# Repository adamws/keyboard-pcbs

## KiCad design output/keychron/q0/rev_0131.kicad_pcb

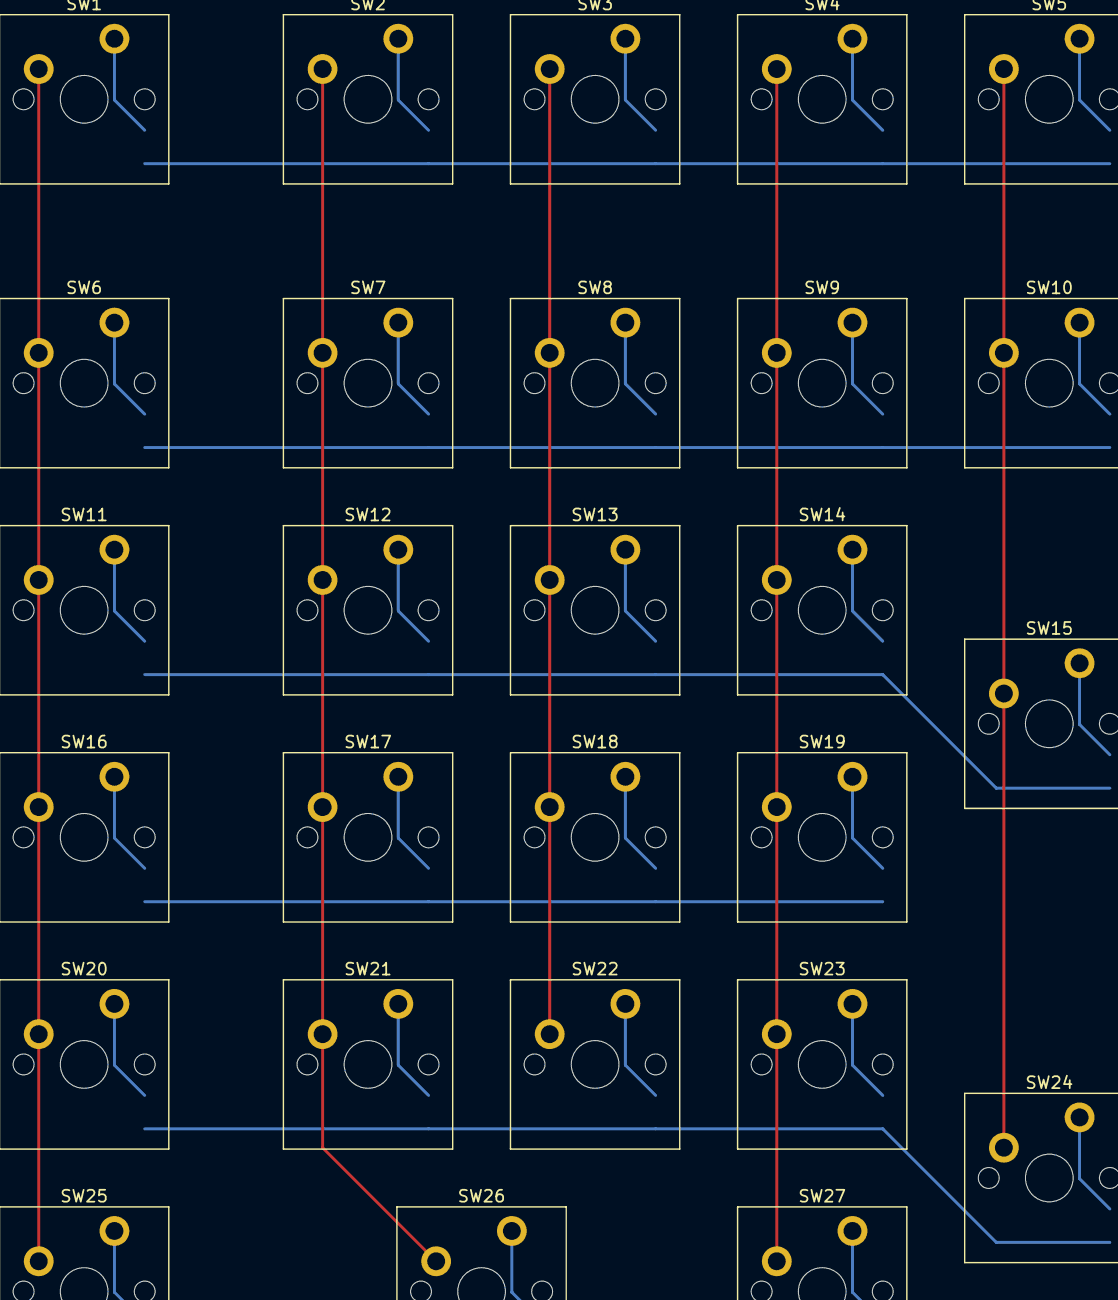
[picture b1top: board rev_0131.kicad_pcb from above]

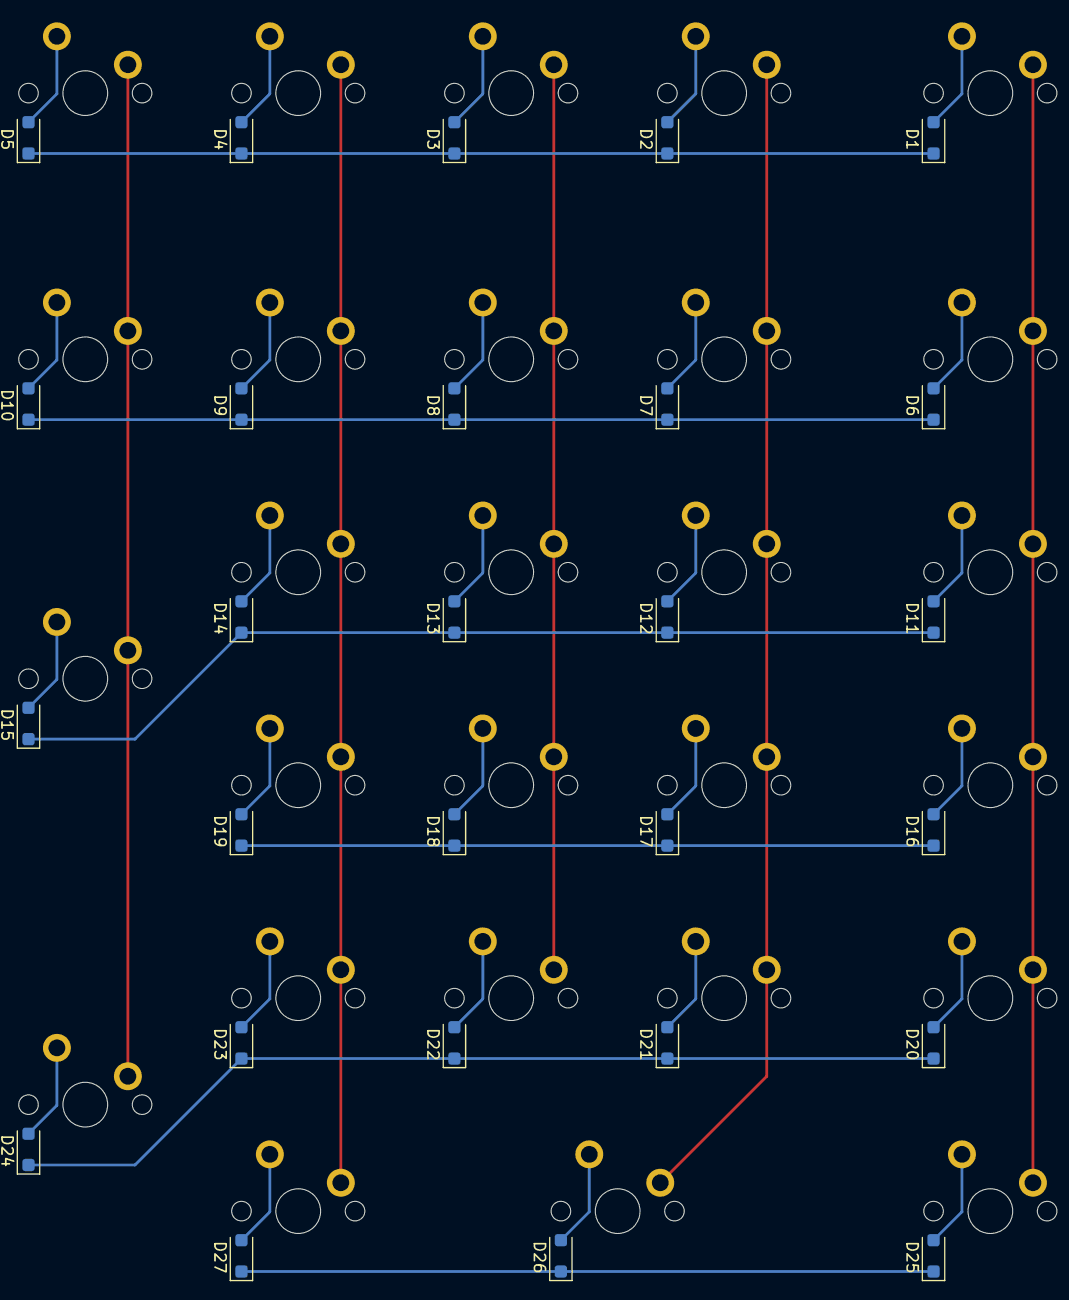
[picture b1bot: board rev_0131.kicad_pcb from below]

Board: 2 copper layers, 54 parts (27 on the bottom side), 38 nets.

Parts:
D1, D2, D3, D4, D5, D6, D7, D8, D9, D10, D11, D12, D13, D14, D15, D16, D17, D18, D19, D20, D21, D22, D23, D24, D25, D26, D27: D_SOD-123F
SW1, SW2, SW3, SW4, SW5, SW6, SW7, SW8, SW9, SW10, SW11, SW12, SW13, SW14, SW15, SW16, SW17, SW18, SW19, SW20, SW21, SW22, SW23, SW24, SW25, SW26, SW27: SW_Cherry_MX_PCB_1.00u

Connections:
COL0: SW1.1, SW6.1, SW11.1, SW16.1, SW20.1, SW25.1
COL1: SW2.1, SW7.1, SW12.1, SW17.1, SW21.1, SW26.1
COL2: SW3.1, SW8.1, SW13.1, SW18.1, SW22.1
COL3: SW4.1, SW9.1, SW14.1, SW19.1, SW23.1, SW27.1
COL4: SW5.1, SW10.1, SW15.1, SW24.1
unnamed: D1.2, SW1.2
unnamed: D2.2, SW2.2
unnamed: D3.2, SW3.2
unnamed: D4.2, SW4.2
unnamed: D5.2, SW5.2
unnamed: D6.2, SW6.2
unnamed: D7.2, SW7.2
unnamed: D8.2, SW8.2
unnamed: D9.2, SW9.2
unnamed: D10.2, SW10.2
unnamed: D11.2, SW11.2
unnamed: D12.2, SW12.2
unnamed: D13.2, SW13.2
unnamed: D14.2, SW14.2
unnamed: D15.2, SW15.2
unnamed: D16.2, SW16.2
unnamed: D17.2, SW17.2
unnamed: D18.2, SW18.2
unnamed: D19.2, SW19.2
unnamed: D20.2, SW20.2
unnamed: D21.2, SW21.2
unnamed: D22.2, SW22.2
unnamed: D23.2, SW23.2
unnamed: D24.2, SW24.2
unnamed: D25.2, SW25.2
unnamed: D26.2, SW26.2
unnamed: D27.2, SW27.2
ROW0: D1.1, D2.1, D3.1, D4.1, D5.1
ROW1: D6.1, D7.1, D8.1, D9.1, D10.1
ROW2: D11.1, D12.1, D13.1, D14.1, D15.1
ROW3: D16.1, D17.1, D18.1, D19.1
ROW4: D20.1, D21.1, D22.1, D23.1, D24.1
ROW5: D25.1, D26.1, D27.1

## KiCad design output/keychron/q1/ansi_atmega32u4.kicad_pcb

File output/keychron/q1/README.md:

## keychron/q1/ansi_atmega32u4

[layout](ansi_atmega32u4-kle.json) - [PCB](ansi_atmega32u4.kicad_pcb)

{:loading="lazy"}

[Open in keyboard-layout-editor](http://www.keyboard-layout-editor.com/##@@_c=#777777;&=0,0%0AESC&_x:0.25&c=#cccccc;&=0,2&=0,3&=0,4&=0,5&_x:0.25&c=#aaaaaa;&=0,6&=0,7&=0,8&=0,9&_x:0.25&c=#cccccc;&=0,10&=0,11&=0,12&=0,13&_x:0.25&c=#aaaaaa;&=4,14&_x:0.25;&=0,14;&@_y:0.25&c=#cccccc;&=1,0&=1,1&=1,2&=1,3&=1,4&=1,5&=1,6&=1,7&=1,8&=1,9&=1,10&=1,11&=1,12&_c=#aaaaaa&w:2;&=1,13&_x:0.25;&=1,14;&@_w:1.5;&=2,0&_c=#cccccc;&=2,1&=2,2&=2,3&=2,4&=2,5&=2,6&=2,7&=2,8&=2,9&=2,10&=2,11&=2,12&_w:1.5;&=2,13&_x:0.25&c=#aaaaaa;&=2,14;&@_w:1.75;&=3,0&_c=#cccccc;&=3,1&=3,2&=3,3&=3,4&=3,5&=3,6&=3,7&=3,8&=3,9&=3,10&=3,11&_c=#777777&w:2.25;&=3,13&_x:0.25&c=#aaaaaa;&=3,14;&@_w:2.25;&=4,0&_c=#cccccc;&=4,2&=4,3&=4,4&=4,5&=4,6&=4,7&=4,8&=4,9&=4,10&=4,11&_c=#aaaaaa&w:1.75;&=4,13;&@_x:14.25&y:-0.75;&=3,12;&@_y:-0.25&w:1.25;&=5,0&_w:1.25;&=5,1&_w:1.25;&=5,2&_c=#cccccc&w:6.25;&=5,6&_c=#aaaaaa;&=5,10&=5,11&=5,12;&@_x:13.25&y:-0.75;&=5,13&=4,12&=5,14)

{:loading="lazy"}

## keychron/q1/ansi_atmega32u4_encoder

[layout](ansi_atmega32u4_encoder-kle.json) - [PCB](ansi_atmega32u4_encoder.kicad_pcb)

{:loading="lazy"}

[Open in keyboard-layout-editor](http://www.keyboard-layout-editor.com/##@@_c=#777777;&=0,0%0AESC&_x:0.25&c=#cccccc;&=0,2&=0,3&=0,4&=0,5&_x:0.25&c=#aaaaaa;&=0,6&=0,7&=0,8&=0,9&_x:0.25&c=#cccccc;&=0,10&=0,11&=0,12&=0,13&_x:0.25&c=#aaaaaa;&=4,14&_x:0.25;&=0,14%0A%0A%0A%0A%0A%0A%0A%0A%0Ae0;&@_y:0.25&c=#cccccc;&=1,0&=1,1&=1,2&=1,3&=1,4&=1,5&=1,6&=1,7&=1,8&=1,9&=1,10&=1,11&=1,12&_c=#aaaaaa&w:2;&=1,13&_x:0.25;&=1,14;&@_w:1.5;&=2,0&_c=#cccccc;&=2,1&=2,2&=2,3&=2,4&=2,5&=2,6&=2,7&=2,8&=2,9&=2,10&=2,11&=2,12&_w:1.5;&=2,13&_x:0.25&c=#aaaaaa;&=2,14;&@_w:1.75;&=3,0&_c=#cccccc;&=3,1&=3,2&=3,3&=3,4&=3,5&=3,6&=3,7&=3,8&=3,9&=3,10&=3,11&_c=#777777&w:2.25;&=3,13&_x:0.25&c=#aaaaaa;&=3,14;&@_w:2.25;&=4,0&_c=#cccccc;&=4,2&=4,3&=4,4&=4,5&=4,6&=4,7&=4,8&=4,9&=4,10&=4,11&_c=#aaaaaa&w:1.75;&=4,13;&@_x:14.25&y:-0.75;&=3,12;&@_y:-0.25&w:1.25;&=5,0&_w:1.25;&=5,1&_w:1.25;&=5,2&_c=#cccccc&w:6.25;&=5,6&_c=#aaaaaa;&=5,10&=5,11&=5,12;&@_x:13.25&y:-0.75;&=5,13&=4,12&=5,14)

{:loading="lazy"}

## keychron/q1/ansi_stm32l432

[layout](ansi_stm32l432-kle.json) - [PCB](ansi_stm32l432.kicad_pcb)

{:loading="lazy"}

[Open in keyboard-layout-editor](http://www.keyboard-layout-editor.com/##@@_c=#777777;&=0,0%0AESC&_x:0.25&c=#cccccc;&=0,1&=0,2&=0,3&=0,4&_x:0.25&c=#aaaaaa;&=0,5&=0,6&=0,7&=0,8&_x:0.25&c=#cccccc;&=0,9&=0,10&=0,11&=0,12&_x:0.25&c=#aaaaaa;&=0,13&_x:0.25;&=0,15;&@_y:0.25&c=#cccccc;&=1,0&=1,1&=1,2&=1,3&=1,4&=1,5&=1,6&=1,7&=1,8&=1,9&=1,10&=1,11&=1,12&_c=#aaaaaa&w:2;&=1,13&_x:0.25;&=1,15;&@_w:1.5;&=2,0&_c=#cccccc;&=2,1&=2,2&=2,3&=2,4&=2,5&=2,6&=2,7&=2,8&=2,9&=2,10&=2,11&=2,12&_w:1.5;&=2,13&_x:0.25&c=#aaaaaa;&=2,15;&@_w:1.75;&=3,0&_c=#cccccc;&=3,1&=3,2&=3,3&=3,4&=3,5&=3,6&=3,7&=3,8&=3,9&=3,10&=3,11&_c=#777777&w:2.25;&=3,13&_x:0.25&c=#aaaaaa;&=3,15;&@_w:2.25;&=4,0&_c=#cccccc;&=4,2&=4,3&=4,4&=4,5&=4,6&=4,7&=4,8&=4,9&=4,10&=4,11&_c=#aaaaaa&w:1.75;&=4,13;&@_x:14.25&y:-0.75&c=#777777;&=4,14;&@_y:-0.25&c=#aaaaaa&w:1.25;&=5,0&_w:1.25;&=5,1&_w:1.25;&=5,2&_c=#cccccc&w:6.25;&=5,6&_c=#aaaaaa;&=5,10&=5,11&=5,12;&@_x:13.25&y:-0.75&c=#777777;&=5,13&=5,14&=5,15)

{:loading="lazy"}

## keychron/q1/ansi_stm32l432_encoder

[layout](ansi_stm32l432_encoder-kle.json) - [PCB](ansi_stm32l432_encoder.kicad_pcb)

{:loading="lazy"}

[Open in keyboard-layout-editor](http://www.keyboard-layout-editor.com/##@@_c=#777777;&=0,0%0AESC&_x:0.25&c=#cccccc;&=0,1&=0,2&=0,3&=0,4&_x:0.25&c=#aaaaaa;&=0,5&=0,6&=0,7&=0,8&_x:0.25&c=#cccccc;&=0,9&=0,10&=0,11&=0,12&_x:0.25&c=#aaaaaa;&=0,13&_x:0.25;&=0,15%0A%0A%0A%0A%0A%0A%0A%0A%0Ae0;&@_y:0.25&c=#cccccc;&=1,0&=1,1&=1,2&=1,3&=1,4&=1,5&=1,6&=1,7&=1,8&=1,9&=1,10&=1,11&=1,12&_c=#aaaaaa&w:2;&=1,13&_x:0.25;&=1,15;&@_w:1.5;&=2,0&_c=#cccccc;&=2,1&=2,2&=2,3&=2,4&=2,5&=2,6&=2,7&=2,8&=2,9&=2,10&=2,11&=2,12&_w:1.5;&=2,13&_x:0.25&c=#aaaaaa;&=2,15;&@_w:1.75;&=3,0&_c=#cccccc;&=3,1&=3,2&=3,3&=3,4&=3,5&=3,6&=3,7&=3,8&=3,9&=3,10&=3,11&_c=#777777&w:2.25;&=3,13&_x:0.25&c=#aaaaaa;&=3,15;&@_w:2.25;&=4,0&_c=#cccccc;&=4,2&=4,3&=4,4&=4,5&=4,6&=4,7&=4,8&=4,9&=4,10&=4,11&_c=#aaaaaa&w:1.75;&=4,13;&@_x:14.25&y:-0.75&c=#777777;&=4,14;&@_y:-0.25&c=#aaaaaa&w:1.25;&=5,0&_w:1.25;&=5,1&_w:1.25;&=5,2&_c=#cccccc&w:6.25;&=5,6&_c=#aaaaaa;&=5,10&=5,11&=5,12;&@_x:13.25&y:-0.75&c=#777777;&=5,13&=5,14&=5,15)

{:loading="lazy"}

## keychron/q1/iso_atmega32u4

[layout](iso_atmega32u4-kle.json) - [PCB](iso_atmega32u4.kicad_pcb)

{:loading="lazy"}

[Open in keyboard-layout-editor](http://www.keyboard-layout-editor.com/##@@_c=#777777;&=0,0%0AESC&_x:0.25&c=#cccccc;&=0,2&=0,3&=0,4&=0,5&_x:0.25&c=#aaaaaa;&=0,6&=0,7&=0,8&=0,9&_x:0.25&c=#cccccc;&=0,10&=0,11&=0,12&=0,13&_x:0.25&c=#aaaaaa;&=4,14&_x:0.25;&=0,14;&@_y:0.25&c=#cccccc;&=1,0&=1,1&=1,2&=1,3&=1,4&=1,5&=1,6&=1,7&=1,8&=1,9&=1,10&=1,11&=1,12&_c=#aaaaaa&w:2;&=1,13&_x:0.25;&=1,14;&@_w:1.5;&=2,0&_c=#cccccc;&=2,1&=2,2&=2,3&=2,4&=2,5&=2,6&=2,7&=2,8&=2,9&=2,10&=2,11&=2,12&_x:0.25&c=#777777&w:1.25&h:2&w2:1.5&h2:1&x2:-0.25;&=2,13&_x:0.25&c=#aaaaaa;&=2,14;&@_w:1.75;&=3,0&_c=#cccccc;&=3,1&=3,2&=3,3&=3,4&=3,5&=3,6&=3,7&=3,8&=3,9&=3,10&=3,11&=3,13&_x:1.5&c=#aaaaaa;&=3,14;&@_w:1.25;&=4,0&_c=#cccccc;&=4,1&=4,2&=4,3&=4,4&=4,5&=4,6&=4,7&=4,8&=4,9&=4,10&=4,11&_c=#aaaaaa&w:1.75;&=4,13;&@_x:14.25&y:-0.75&c=#777777;&=3,12;&@_y:-0.25&c=#aaaaaa&w:1.25;&=5,0&_w:1.25;&=5,1&_w:1.25;&=5,2&_c=#cccccc&w:6.25;&=5,6&_c=#aaaaaa;&=5,10&=5,11&=5,12;&@_x:13.25&y:-0.75&c=#777777;&=5,13&=4,12&=5,14)

{:loading="lazy"}

## keychron/q1/iso_atmega32u4_encoder

[layout](iso_atmega32u4_encoder-kle.json) - [PCB](iso_atmega32u4_encoder.kicad_pcb)

{:loading="lazy"}

[Open in keyboard-layout-editor](http://www.keyboard-layout-editor.com/##@@_c=#777777;&=0,0%0AESC&_x:0.25&c=#cccccc;&=0,2&=0,3&=0,4&=0,5&_x:0.25&c=#aaaaaa;&=0,6&=0,7&=0,8&=0,9&_x:0.25&c=#cccccc;&=0,10&=0,11&=0,12&=0,13&_x:0.25&c=#aaaaaa;&=4,14&_x:0.25;&=0,14%0A%0A%0A%0A%0A%0A%0A%0A%0Ae0;&@_y:0.25&c=#cccccc;&=1,0&=1,1&=1,2&=1,3&=1,4&=1,5&=1,6&=1,7&=1,8&=1,9&=1,10&=1,11&=1,12&_c=#aaaaaa&w:2;&=1,13&_x:0.25;&=1,14;&@_w:1.5;&=2,0&_c=#cccccc;&=2,1&=2,2&=2,3&=2,4&=2,5&=2,6&=2,7&=2,8&=2,9&=2,10&=2,11&=2,12&_x:0.25&c=#777777&w:1.25&h:2&w2:1.5&h2:1&x2:-0.25;&=2,13&_x:0.25&c=#aaaaaa;&=2,14;&@_w:1.75;&=3,0&_c=#cccccc;&=3,1&=3,2&=3,3&=3,4&=3,5&=3,6&=3,7&=3,8&=3,9&=3,10&=3,11&=3,13&_x:1.5&c=#aaaaaa;&=3,14;&@_w:1.25;&=4,0&_c=#cccccc;&=4,1&=4,2&=4,3&=4,4&=4,5&=4,6&=4,7&=4,8&=4,9&=4,10&=4,11&_c=#aaaaaa&w:1.75;&=4,13;&@_x:14.25&y:-0.75&c=#777777;&=3,12;&@_y:-0.25&c=#aaaaaa&w:1.25;&=5,0&_w:1.25;&=5,1&_w:1.25;&=5,2&_c=#cccccc&w:6.25;&=5,6&_c=#aaaaaa;&=5,10&=5,11&=5,12;&@_x:13.25&y:-0.75&c=#777777;&=5,13&=4,12&=5,14)

{:loading="lazy"}

## keychron/q1/iso_stm32l432

[layout](iso_stm32l432-kle.json) - [PCB](iso_stm32l432.kicad_pcb)

{:loading="lazy"}

[Open in keyboard-layout-editor](http://www.keyboard-layout-editor.com/##@@_c=#777777;&=0,0%0AESC&_x:0.25&c=#cccccc;&=0,1&=0,2&=0,3&=0,4&_x:0.25&c=#aaaaaa;&=0,5&=0,6&=0,7&=0,8&_x:0.25&c=#cccccc;&=0,9&=0,10&=0,11&=0,12&_x:0.25&c=#aaaaaa;&=0,13&_x:0.25;&=0,15;&@_y:0.25&c=#cccccc;&=1,0&=1,1&=1,2&=1,3&=1,4&=1,5&=1,6&=1,7&=1,8&=1,9&=1,10&=1,11&=1,12&_c=#aaaaaa&w:2;&=1,13&_x:0.25;&=1,15;&@_w:1.5;&=2,0&_c=#cccccc;&=2,1&=2,2&=2,3&=2,4&=2,5&=2,6&=2,7&=2,8&=2,9&=2,10&=2,11&=2,12&_x:0.25&c=#777777&w:1.25&h:2&w2:1.5&h2:1&x2:-0.25;&=2,13&_x:0.25&c=#aaaaaa;&=2,15;&@_w:1.75;&=3,0&_c=#cccccc;&=3,1&=3,2&=3,3&=3,4&=3,5&=3,6&=3,7&=3,8&=3,9&=3,10&=3,11&=3,13&_x:1.5&c=#aaaaaa;&=3,15;&@_w:1.25;&=4,0&_c=#cccccc;&=4,1&=4,2&=4,3&=4,4&=4,5&=4,6&=4,7&=4,8&=4,9&=4,10&=4,11&_c=#aaaaaa&w:1.75;&=4,13;&@_x:14.25&y:-0.75&c=#777777;&=4,14;&@_y:-0.25&c=#aaaaaa&w:1.25;&=5,0&_w:1.25;&=5,1&_w:1.25;&=5,2&_c=#cccccc&w:6.25;&=5,6&_c=#aaaaaa;&=5,10&=5,11&=5,12;&@_x:13.25&y:-0.75&c=#777777;&=5,13&=5,14&=5,15)

{:loading="lazy"}

## keychron/q1/iso_stm32l432_encoder

[layout](iso_stm32l432_encoder-kle.json) - [PCB](iso_stm32l432_encoder.kicad_pcb)

{:loading="lazy"}

[Open in keyboard-layout-editor](http://www.keyboard-layout-editor.com/##@@_c=#777777;&=0,0%0AESC&_x:0.25&c=#cccccc;&=0,1&=0,2&=0,3&=0,4&_x:0.25&c=#aaaaaa;&=0,5&=0,6&=0,7&=0,8&_x:0.25&c=#cccccc;&=0,9&=0,10&=0,11&=0,12&_x:0.25&c=#aaaaaa;&=0,13&_x:0.25;&=0,15%0A%0A%0A%0A%0A%0A%0A%0A%0Ae0;&@_y:0.25&c=#cccccc;&=1,0&=1,1&=1,2&=1,3&=1,4&=1,5&=1,6&=1,7&=1,8&=1,9&=1,10&=1,11&=1,12&_c=#aaaaaa&w:2;&=1,13&_x:0.25;&=1,15;&@_w:1.5;&=2,0&_c=#cccccc;&=2,1&=2,2&=2,3&=2,4&=2,5&=2,6&=2,7&=2,8&=2,9&=2,10&=2,11&=2,12&_x:0.25&c=#777777&w:1.25&h:2&w2:1.5&h2:1&x2:-0.25;&=2,13&_x:0.25&c=#aaaaaa;&=2,15;&@_w:1.75;&=3,0&_c=#cccccc;&=3,1&=3,2&=3,3&=3,4&=3,5&=3,6&=3,7&=3,8&=3,9&=3,10&=3,11&=3,13&_x:1.5&c=#aaaaaa;&=3,15;&@_w:1.25;&=4,0&_c=#cccccc;&=4,1&=4,2&=4,3&=4,4&=4,5&=4,6&=4,7&=4,8&=4,9&=4,10&=4,11&_c=#aaaaaa&w:1.75;&=4,13;&@_x:14.25&y:-0.75&c=#777777;&=4,14;&@_y:-0.25&c=#aaaaaa&w:1.25;&=5,0&_w:1.25;&=5,1&_w:1.25;&=5,2&_c=#cccccc&w:6.25;&=5,6&_c=#aaaaaa;&=5,10&=5,11&=5,12;&@_x:13.25&y:-0.75&c=#777777;&=5,13&=5,14&=5,15)

{:loading="lazy"}

## keychron/q1/jis_stm32l432

[layout](jis_stm32l432-kle.json) - [PCB](jis_stm32l432.kicad_pcb)

{:loading="lazy"}

[Open in keyboard-layout-editor](http://www.keyboard-layout-editor.com/##@@_c=#777777;&=0,0%0AESC&_x:0.25&c=#cccccc;&=0,1&=0,2&=0,3&=0,4&_x:0.25&c=#aaaaaa;&=0,5&=0,6&=0,7&=0,8&_x:0.25&c=#cccccc;&=0,9&=0,10&=0,11&=0,12&_x:0.25&c=#aaaaaa;&=0,13&_x:0.25;&=0,15;&@_y:0.25;&=1,0&_c=#cccccc;&=1,1&=1,2&=1,3&=1,4&=1,5&=1,6&=1,7&=1,8&=1,9&=1,10&=1,11&=1,12&=1,13&_c=#aaaaaa;&=1,14&_x:0.25;&=1,15;&@_w:1.5;&=2,0&_c=#cccccc;&=2,1&=2,2&=2,3&=2,4&=2,5&=2,6&=2,7&=2,8&=2,9&=2,10&=2,11&=2,12&_x:0.25&c=#777777&w:1.25&h:2&w2:1.5&h2:1&x2:-0.25;&=2,13&_x:0.25&c=#aaaaaa;&=2,15;&@_w:1.75;&=3,0&_c=#cccccc;&=3,1&=3,2&=3,3&=3,4&=3,5&=3,6&=3,7&=3,8&=3,9&=3,10&=3,11&_c=#aaaaaa;&=3,13&_x:1.5;&=3,15;&@_w:2.25;&=4,0&_c=#cccccc;&=4,2&=4,3&=4,4&=4,5&=4,6&=4,7&=4,8&=4,9&=4,10&=4,11&=4,12&_c=#aaaaaa;&=4,13&_c=#777777;&=4,14;&@_c=#aaaaaa&w:1.25;&=5,0&=5,1&_w:1.25;&=5,2&=5,3&_c=#cccccc&w:4.5;&=5,6&_c=#aaaaaa&w:1.25;&=5,9&=5,10&=5,11&=5,12&_c=#777777;&=5,13&=5,14&=5,15)

{:loading="lazy"}

## keychron/q1/jis_stm32l432_encoder

[layout](jis_stm32l432_encoder-kle.json) - [PCB](jis_stm32l432_encoder.kicad_pcb)

{:loading="lazy"}

[Open in keyboard-layout-editor](http://www.keyboard-layout-editor.com/##@@_c=#777777;&=0,0%0AESC&_x:0.25&c=#cccccc;&=0,1&=0,2&=0,3&=0,4&_x:0.25&c=#aaaaaa;&=0,5&=0,6&=0,7&=0,8&_x:0.25&c=#cccccc;&=0,9&=0,10&=0,11&=0,12&_x:0.25&c=#aaaaaa;&=0,13&_x:0.25;&=0,15%0A%0A%0A%0A%0A%0A%0A%0A%0Ae0;&@_y:0.25;&=1,0&_c=#cccccc;&=1,1&=1,2&=1,3&=1,4&=1,5&=1,6&=1,7&=1,8&=1,9&=1,10&=1,11&=1,12&=1,13&_c=#aaaaaa;&=1,14&_x:0.25;&=1,15;&@_w:1.5;&=2,0&_c=#cccccc;&=2,1&=2,2&=2,3&=2,4&=2,5&=2,6&=2,7&=2,8&=2,9&=2,10&=2,11&=2,12&_x:0.25&c=#777777&w:1.25&h:2&w2:1.5&h2:1&x2:-0.25;&=2,13&_x:0.25&c=#aaaaaa;&=2,15;&@_w:1.75;&=3,0&_c=#cccccc;&=3,1&=3,2&=3,3&=3,4&=3,5&=3,6&=3,7&=3,8&=3,9&=3,10&=3,11&_c=#aaaaaa;&=3,13&_x:1.5;&=3,15;&@_w:2.25;&=4,0&_c=#cccccc;&=4,2&=4,3&=4,4&=4,5&=4,6&=4,7&=4,8&=4,9&=4,10&=4,11&=4,12&_c=#aaaaaa;&=4,13&_c=#777777;&=4,14;&@_c=#aaaaaa&w:1.25;&=5,0&=5,1&_w:1.25;&=5,2&=5,3&_c=#cccccc&w:4.5;&=5,6&_c=#aaaaaa&w:1.25;&=5,9&=5,10&=5,11&=5,12&_c=#777777;&=5,13&=5,14&=5,15)

{:loading="lazy"}

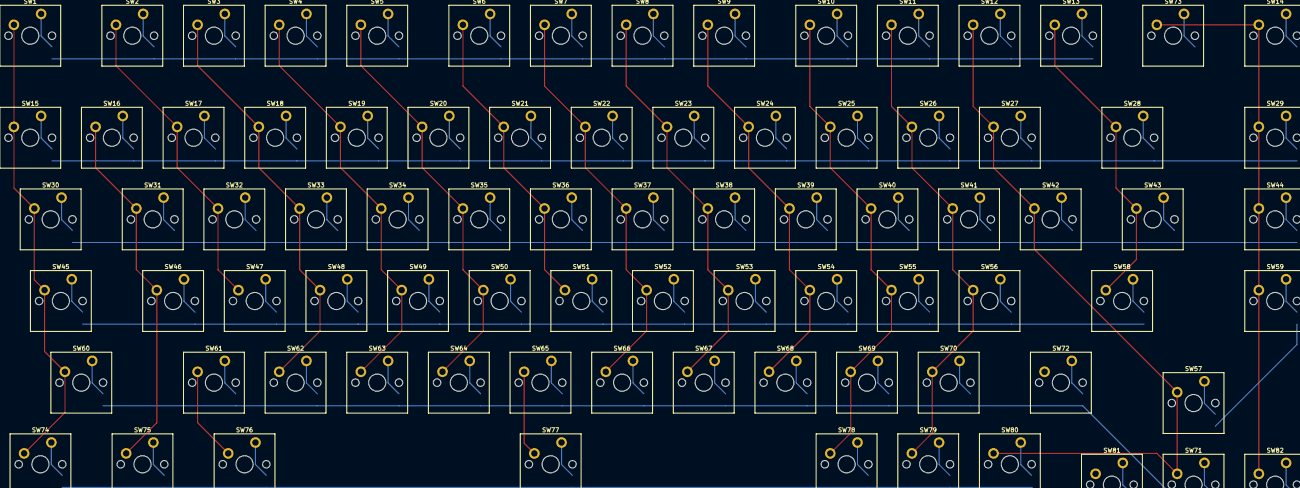
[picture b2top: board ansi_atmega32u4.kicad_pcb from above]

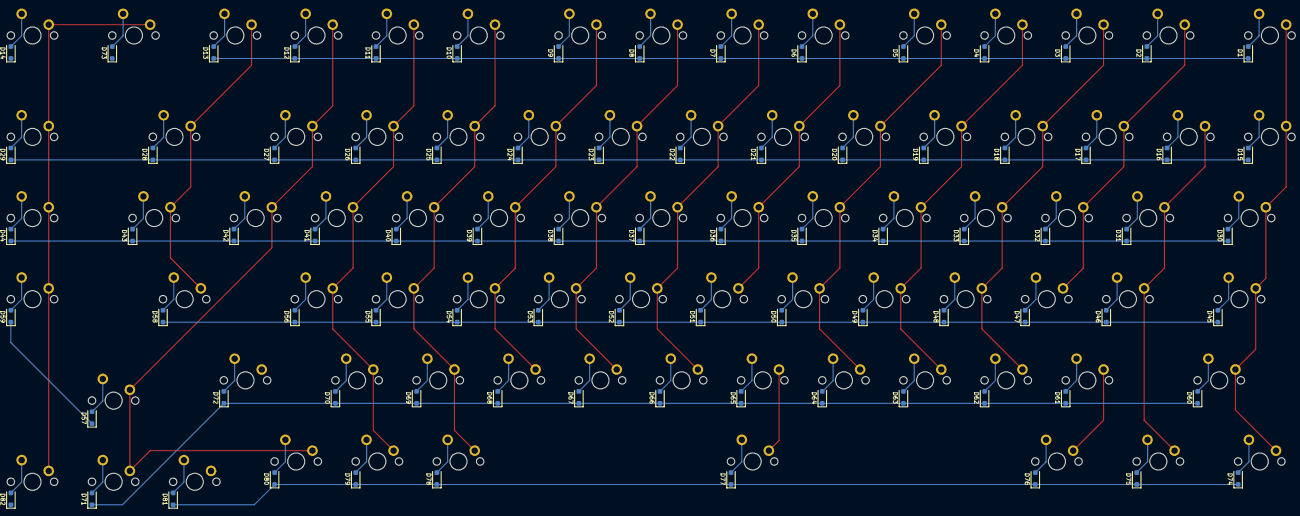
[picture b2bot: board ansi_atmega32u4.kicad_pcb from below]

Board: 2 copper layers, 164 parts (82 on the bottom side), 103 nets.

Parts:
D1, D2, D3, D4, D5, D6, D7, D8, D9, D10, D11, D12, D13, D14, D15, D16, D17, D18, D19, D20, D21, D22, D23, D24, D25, D26, D27, D28, D29, D30, D31, D32, D33, D34, D35, D36, D37, D38, D39, D40, D41, D42, D43, D44, D45, D46, D47, D48, D49, D50, D51, D52, D53, D54, D55, D56, D57, D58, D59, D60, D61, D62, D63, D64, D65, D66, D67, D68, D69, D70, D71, D72, D73, D74, D75, D76, D77, D78, D79, D80, D81, D82: D_SOD-123F
SW1, SW2, SW3, SW4, SW5, SW6, SW7, SW8, SW9, SW10, SW11, SW12, SW13, SW14, SW15, SW16, SW17, SW18, SW19, SW20, SW21, SW22, SW23, SW24, SW25, SW26, SW27, SW28, SW29, SW30, SW31, SW32, SW33, SW34, SW35, SW36, SW37, SW38, SW39, SW40, SW41, SW42, SW43, SW44, SW45, SW46, SW47, SW48, SW49, SW50, SW51, SW52, SW53, SW54, SW55, SW56, SW57, SW58, SW59, SW60, SW61, SW62, SW63, SW64, SW65, SW66, SW67, SW68, SW69, SW70, SW71, SW72, SW73, SW74, SW75, SW76, SW77, SW78, SW79, SW80, SW81, SW82: SW_Cherry_MX_PCB_1.00u

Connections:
COL0: SW1.1, SW15.1, SW30.1, SW45.1, SW60.1, SW74.1
COL1: SW16.1, SW31.1, SW46.1, SW75.1
COL2: SW2.1, SW17.1, SW32.1, SW47.1, SW61.1, SW76.1
COL3: SW3.1, SW18.1, SW33.1, SW48.1, SW62.1
COL4: SW4.1, SW19.1, SW34.1, SW49.1, SW63.1
COL5: SW5.1, SW20.1, SW35.1, SW50.1, SW64.1
COL6: SW6.1, SW21.1, SW36.1, SW51.1, SW65.1, SW77.1
COL7: SW7.1, SW22.1, SW37.1, SW52.1, SW66.1
COL8: SW8.1, SW23.1, SW38.1, SW53.1, SW67.1
COL9: SW9.1, SW24.1, SW39.1, SW54.1, SW68.1
COL10: SW10.1, SW25.1, SW40.1, SW55.1, SW69.1, SW78.1
COL11: SW11.1, SW26.1, SW41.1, SW56.1, SW70.1, SW79.1
COL12: SW12.1, SW27.1, SW42.1, SW57.1, SW71.1, SW80.1
COL13: SW13.1, SW28.1, SW43.1, SW58.1, SW72.1, SW81.1
COL14: SW14.1, SW29.1, SW44.1, SW59.1, SW73.1, SW82.1
unnamed: D1.2, SW1.2
unnamed: D2.2, SW2.2
unnamed: D3.2, SW3.2
unnamed: D4.2, SW4.2
unnamed: D5.2, SW5.2
unnamed: D6.2, SW6.2
unnamed: D7.2, SW7.2
unnamed: D8.2, SW8.2
unnamed: D9.2, SW9.2
unnamed: D10.2, SW10.2
unnamed: D11.2, SW11.2
unnamed: D12.2, SW12.2
unnamed: D13.2, SW13.2
unnamed: D14.2, SW14.2
unnamed: D15.2, SW15.2
unnamed: D16.2, SW16.2
unnamed: D17.2, SW17.2
unnamed: D18.2, SW18.2
unnamed: D19.2, SW19.2
unnamed: D20.2, SW20.2
unnamed: D21.2, SW21.2
unnamed: D22.2, SW22.2
unnamed: D23.2, SW23.2
unnamed: D24.2, SW24.2
unnamed: D25.2, SW25.2
unnamed: D26.2, SW26.2
unnamed: D27.2, SW27.2
unnamed: D28.2, SW28.2
unnamed: D29.2, SW29.2
unnamed: D30.2, SW30.2
unnamed: D31.2, SW31.2
unnamed: D32.2, SW32.2
unnamed: D33.2, SW33.2
unnamed: D34.2, SW34.2
unnamed: D35.2, SW35.2
unnamed: D36.2, SW36.2
unnamed: D37.2, SW37.2
unnamed: D38.2, SW38.2
unnamed: D39.2, SW39.2
unnamed: D40.2, SW40.2
unnamed: D41.2, SW41.2
unnamed: D42.2, SW42.2
unnamed: D43.2, SW43.2
unnamed: D44.2, SW44.2
unnamed: D45.2, SW45.2
unnamed: D46.2, SW46.2
unnamed: D47.2, SW47.2
unnamed: D48.2, SW48.2
unnamed: D49.2, SW49.2
unnamed: D50.2, SW50.2
unnamed: D51.2, SW51.2
unnamed: D52.2, SW52.2
unnamed: D53.2, SW53.2
unnamed: D54.2, SW54.2
unnamed: D55.2, SW55.2
unnamed: D56.2, SW56.2
unnamed: D57.2, SW57.2
unnamed: D58.2, SW58.2
unnamed: D59.2, SW59.2
unnamed: D60.2, SW60.2
unnamed: D61.2, SW61.2
unnamed: D62.2, SW62.2
unnamed: D63.2, SW63.2
unnamed: D64.2, SW64.2
unnamed: D65.2, SW65.2
unnamed: D66.2, SW66.2
unnamed: D67.2, SW67.2
unnamed: D68.2, SW68.2
unnamed: D69.2, SW69.2
unnamed: D70.2, SW70.2
unnamed: D71.2, SW71.2
unnamed: D72.2, SW72.2
unnamed: D73.2, SW73.2
unnamed: D74.2, SW74.2
unnamed: D75.2, SW75.2
unnamed: D76.2, SW76.2
unnamed: D77.2, SW77.2
unnamed: D78.2, SW78.2
unnamed: D79.2, SW79.2
unnamed: D80.2, SW80.2
unnamed: D81.2, SW81.2
unnamed: D82.2, SW82.2
ROW0: D1.1, D2.1, D3.1, D4.1, D5.1, D6.1, D7.1, D8.1, D9.1, D10.1, D11.1, D12.1, D13.1, D14.1
ROW1: D15.1, D16.1, D17.1, D18.1, D19.1, D20.1, D21.1, D22.1, D23.1, D24.1, D25.1, D26.1, D27.1, D28.1, D29.1
ROW2: D30.1, D31.1, D32.1, D33.1, D34.1, D35.1, D36.1, D37.1, D38.1, D39.1, D40.1, D41.1, D42.1, D43.1, D44.1
ROW3: D45.1, D46.1, D47.1, D48.1, D49.1, D50.1, D51.1, D52.1, D53.1, D54.1, D55.1, D56.1, D57.1, D58.1, D59.1
ROW4: D60.1, D61.1, D62.1, D63.1, D64.1, D65.1, D66.1, D67.1, D68.1, D69.1, D70.1, D71.1, D72.1, D73.1
ROW5: D74.1, D75.1, D76.1, D77.1, D78.1, D79.1, D80.1, D81.1, D82.1
